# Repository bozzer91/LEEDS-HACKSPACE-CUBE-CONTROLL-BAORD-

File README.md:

# LEEDS HACKSPACE CUBE CONTROLL BOARD

# This READ me is a work in progress, please check back soon  :

This repository is for the new control board for the Leeds hackspace Cube art installation, this board will take input from a pc and output commands to the 16 Lines of addressable LEDS at 5v logic.  

wiring diagram visualisation ( not final revision) 

( the cube ) 

## Board info :

### Purpose : 
This control board is designed to take a Raspberry pi pico / pico-W and convert 16 data lines from 3v3 voltage to 5volt data and output this to the 16 LED strings of the Hackspace Cube. this board also includes extra ports for expansion and other functions for future upgrades. the board is about 10cm by 6cm and is deigned to be placed into an encloser with the users connectors of choice attached and soldered onto the PCB DATA outputs.   

### Reference text: 

The test points for the DATA and GPIO are as follows.
Data: to the left-hand side of the resistor above " D-1 example " the label. the left hand side is 5v

GPIO: test point to the right-hand side of the resistor below the labelling. with the left hand side being 3v3 volts

see below for the visual.

### Spare pin header :
The pin header by pins 16-28 are spare for future expansion of the cube the numbers listed on the PCB are the GPIO numbers of the pico. There are extra GND pins to the right of this pin header.

### Smothing caps :
There are 100nf smoothing caps on the main voltage rails for 5v and 3v3 these are set at locations around the board first set next to the pico and then one set pure bank of 4 logic shifters. ( see below images for examples )

### Main outputs : 
The controller board has two main Data output connectors in the form of two sets of pinheaders to connect to the users connector of choice this also mimicked the original breadboard design and allows for drop in replacement if required using the original ribbon cables. 

Connector 1 = Data 1-8 plus one GND pin
Connector 2 = Data 9-16 plus one GND pin

### Power : 
This controller board is powered by the Pico's usb input port. 

## History of this project: 

So some history of this project. back in 2022 ( give or take a covid lockdown ) it was found that the original micro controller board for the cube had broken. work was undertaken to revers engineer this board and make a replacement for 2022 Leeds lightweight. roll on to 2025 and we are still using the fear inducing Bread board that looks like something you find in a suite case in a mission impossible film that needs defusing ( see below image ) so when packing down the cube i decided to make a pcb to replace this and help move the Cube to a more user friendly plug and play design. 

BREAD BOARD

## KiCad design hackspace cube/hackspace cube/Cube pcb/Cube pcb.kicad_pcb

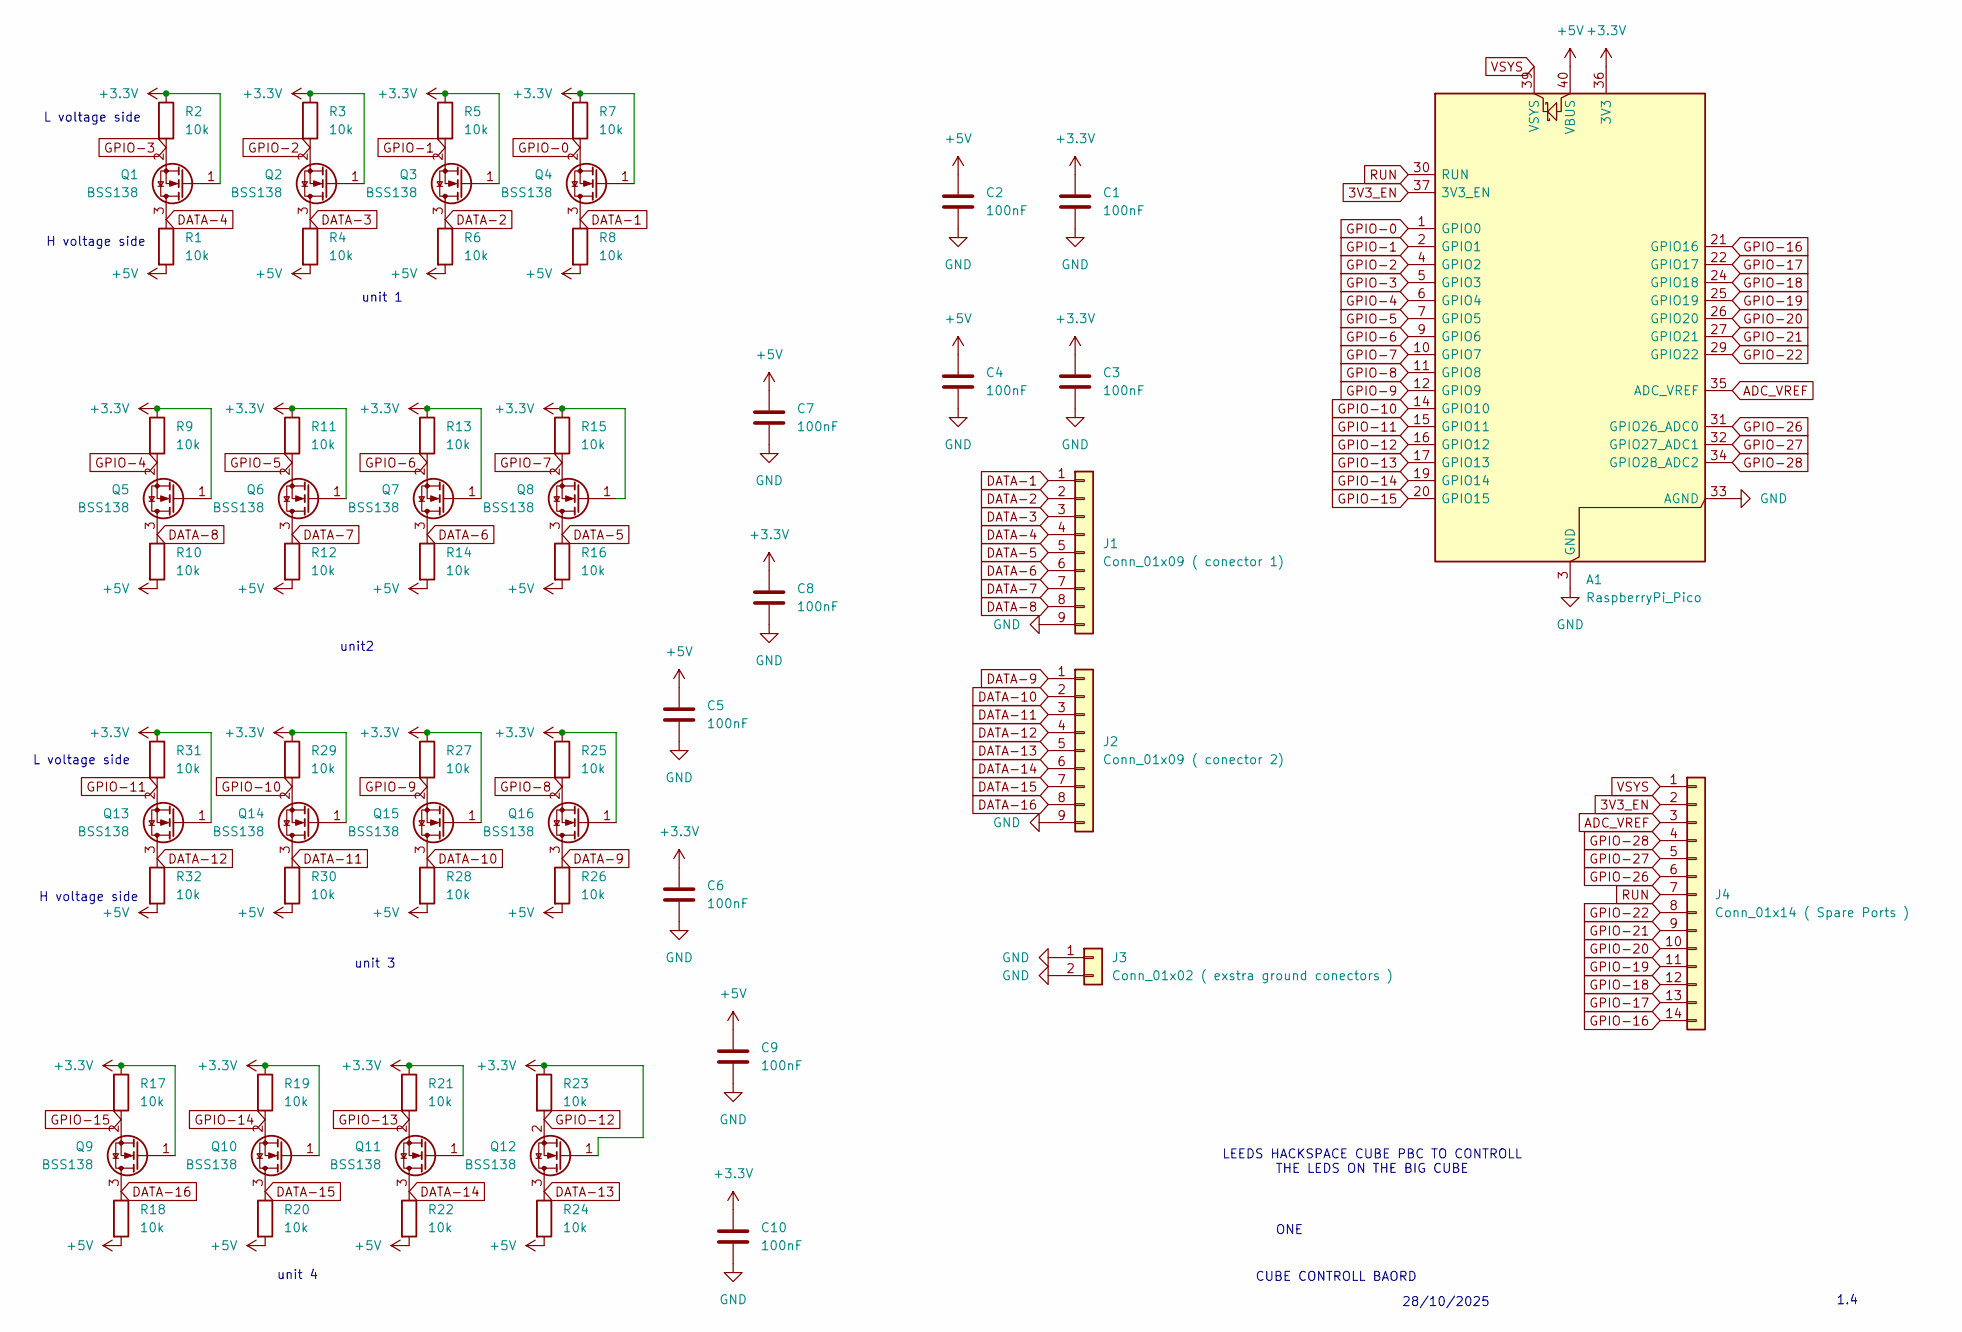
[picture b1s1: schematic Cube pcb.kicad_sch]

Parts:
A1: RaspberryPi_Pico; RaspberryPi_Pico_Common_Unspecified
C1, C2, C3, C4, C5, C6, C7, C8, C9, C10: 100nF; C_0805_2012Metric
J1: Conn_01x09 ( conector 1); PinHeader_1x09_P2.54mm_Vertical
J2: Conn_01x09 ( conector 2); PinHeader_1x09_P2.54mm_Vertical
J3: Conn_01x02 ( exstra ground conectors ); PinHeader_1x02_P2.54mm_Vertical
J4: Conn_01x14 ( Spare Ports ); PinHeader_1x14_P2.54mm_Vertical
Q1, Q2, Q3, Q4, Q5, Q6, Q7, Q8, Q9, Q10, Q11, Q12, Q13, Q14, Q15, Q16: BSS138; SOT-23
R1, R2, R3, R4, R5, R6, R7, R8, R9, R10, R11, R12, R13, R14, R15, R16, R17, R18, R19, R20, R21, R22, R23, R24, R25, R26, R27, R28, R29, R30, R31, R32: 10k; R_0805_2012Metric

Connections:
3V3_EN: A1.37 (3V3_EN), J4.2
+3.3V: A1.36 (3V3), C1.1, C3.1, C6.1, C8.1, C10.1, Q1.1 (G), Q2.1 (G), Q3.1 (G), Q4.1 (G), Q5.1 (G), Q6.1 (G), Q7.1 (G), Q8.1 (G), Q9.1 (G), Q10.1 (G), Q11.1 (G), Q12.1 (G), Q13.1 (G), Q14.1 (G), Q15.1 (G), Q16.1 (G), R2.1, R3.1, R5.1, R7.1, R9.1, R11.1, R13.1, R15.1, R17.1, R19.1, R21.1, R23.1, R25.1, R27.1, R29.1, R31.1
+5V: A1.40 (VBUS), C2.1, C4.1, C5.1, C7.1, C9.1, R1.2, R4.2, R6.2, R8.2, R10.2, R12.2, R14.2, R16.2, R18.2, R20.2, R22.2, R24.2, R26.2, R28.2, R30.2, R32.2
ADC_VREF: A1.35 (ADC_VREF), J4.3
DATA-1: J1.1, Q4.3 (D), R8.1
DATA-2: J1.2, Q3.3 (D), R6.1
DATA-3: J1.3, Q2.3 (D), R4.1
DATA-4: J1.4, Q1.3 (D), R1.1
DATA-5: J1.5, Q8.3 (D), R16.1
DATA-6: J1.6, Q7.3 (D), R14.1
DATA-7: J1.7, Q6.3 (D), R12.1
DATA-8: J1.8, Q5.3 (D), R10.1
DATA-9: J2.1, Q16.3 (D), R26.1
DATA-10: J2.2, Q15.3 (D), R28.1
DATA-11: J2.3, Q14.3 (D), R30.1
DATA-12: J2.4, Q13.3 (D), R32.1
DATA-13: J2.5, Q12.3 (D), R24.1
DATA-14: J2.6, Q11.3 (D), R22.1
DATA-15: J2.7, Q10.3 (D), R20.1
DATA-16: J2.8, Q9.3 (D), R18.1
GND: A1.3 (GND), A1.8 (GND), A1.13 (GND), A1.18 (GND), A1.23 (GND), A1.28 (GND), A1.33 (AGND), A1.38 (GND), C1.2, C2.2, C3.2, C4.2, C5.2, C6.2, C7.2, C8.2, C9.2, C10.2, J1.9, J2.9, J3.1, J3.2
GPIO-0: A1.1 (GPIO0), Q4.2 (S), R7.2
GPIO-1: A1.2 (GPIO1), Q3.2 (S), R5.2
GPIO-2: A1.4 (GPIO2), Q2.2 (S), R3.2
GPIO-3: A1.5 (GPIO3), Q1.2 (S), R2.2
GPIO-4: A1.6 (GPIO4), Q5.2 (S), R9.2
GPIO-5: A1.7 (GPIO5), Q6.2 (S), R11.2
GPIO-6: A1.9 (GPIO6), Q7.2 (S), R13.2
GPIO-7: A1.10 (GPIO7), Q8.2 (S), R15.2
GPIO-8: A1.11 (GPIO8), Q16.2 (S), R25.2
GPIO-9: A1.12 (GPIO9), Q15.2 (S), R27.2
GPIO-10: A1.14 (GPIO10), Q14.2 (S), R29.2
GPIO-11: A1.15 (GPIO11), Q13.2 (S), R31.2
GPIO-12: A1.16 (GPIO12), Q12.2 (S), R23.2
GPIO-13: A1.17 (GPIO13), Q11.2 (S), R21.2
GPIO-14: A1.19 (GPIO14), Q10.2 (S), R19.2
GPIO-15: A1.20 (GPIO15), Q9.2 (S), R17.2
GPIO-16: A1.21 (GPIO16), J4.14
GPIO-17: A1.22 (GPIO17), J4.13
GPIO-18: A1.24 (GPIO18), J4.12
GPIO-19: A1.25 (GPIO19), J4.11
GPIO-20: A1.26 (GPIO20), J4.10
GPIO-21: A1.27 (GPIO21), J4.9
GPIO-22: A1.29 (GPIO22), J4.8
GPIO-26: A1.31 (GPIO26_ADC0), J4.6
GPIO-27: A1.32 (GPIO27_ADC1), J4.5
GPIO-28: A1.34 (GPIO28_ADC2), J4.4
RUN: A1.30 (RUN), J4.7
VSYS: A1.39 (VSYS), J4.1

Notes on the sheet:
CUBE CONTROLL BAORD
unit 4
LEEDS HACKSPACE CUBE PBC TO CONTROLL THE LEDS ON THE BIG CUBE
unit 1
unit2
28/10/2025
unit 3
1.4
H voltage side
ONE
L voltage side

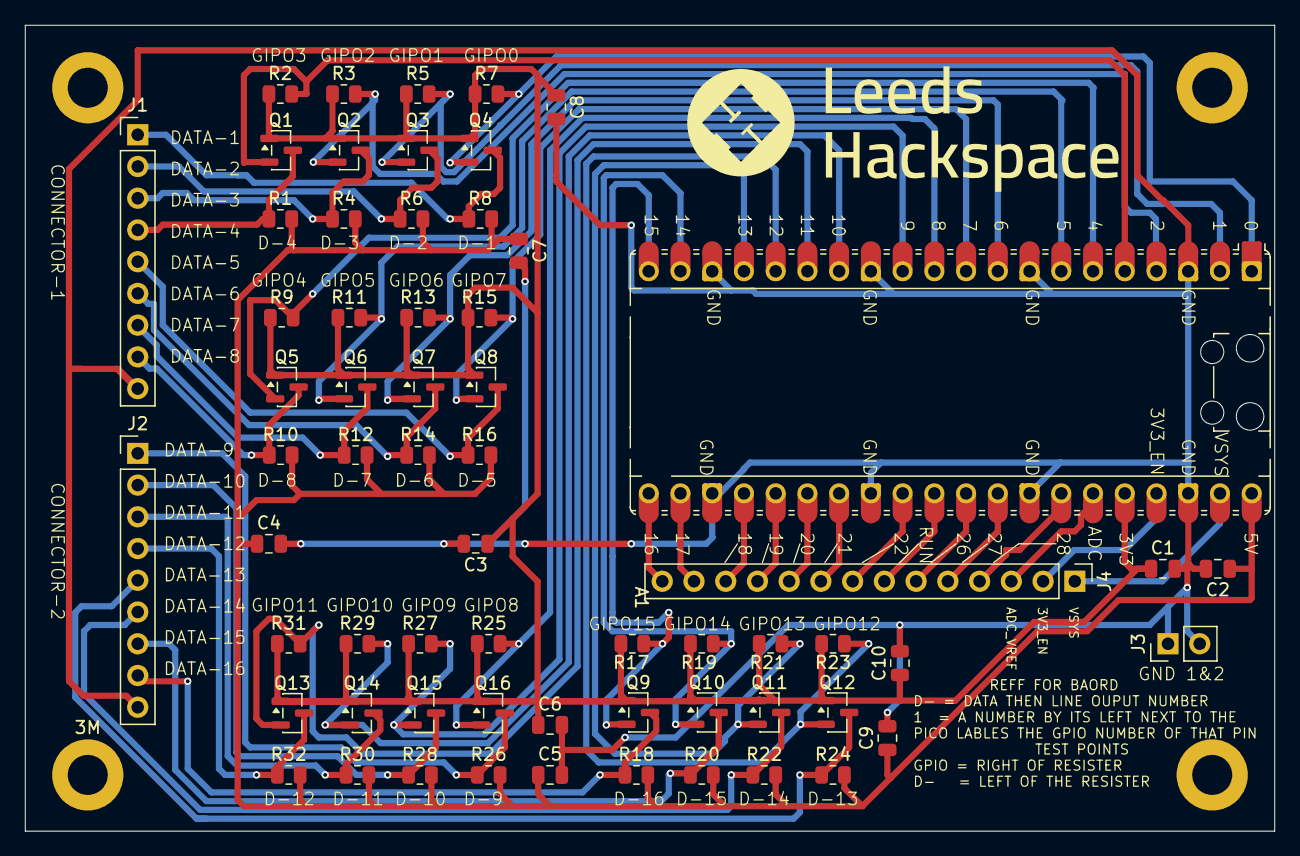
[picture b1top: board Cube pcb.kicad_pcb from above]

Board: 2 copper layers, 100.0 x 64.5 mm, 64 parts (0 on the bottom side), 49 nets.

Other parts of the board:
3M: MountingHole_3.2mm_M3_ISO7380_Pad

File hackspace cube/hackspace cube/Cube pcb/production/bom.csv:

Designator,Footprint,Quantity,Value,LCSC Part #
"_3, _2, ",,3,,
A1,RaspberryPi_Pico_Common_Unspecified,1,RaspberryPi_Pico,
"C1, C10, C2, C3, C4, C5, C6, C7, C8, C9",0805,10,100nF,
J1,PinHeader_1x09_P2.54mm_Vertical,1,Conn_01x09 ( conector 1),
J2,PinHeader_1x09_P2.54mm_Vertical,1,Conn_01x09 ( conector 2),
J3,PinHeader_1x02_P2.54mm_Vertical,1,Conn_01x02 ( exstra ground conectors ),
J4,PinHeader_1x14_P2.54mm_Vertical,1,Conn_01x14 ( Spare Ports ),
"Q1, Q10, Q11, Q12, Q13, Q14, Q15, Q16, Q2, Q3, Q4, Q5, Q6, Q7, Q8, Q9",SOT-23,16,BSS138,
"R1, R10, R11, R12, R13, R14, R15, R16, R17, R18, R19, R2, R20, R21, R22, R23, R24, R25, R26, R27, R28, R29, R3, R30, R31, R32, R4, R5, R6, R7, R8, R9",0805,32,10k,

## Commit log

2025-10-25 Update README.md
    EDIT READ ME
2025-10-25 CUBE KI CAD FILES
2025-10-25 rev 1.1
    added caps
2025-10-25 rev1.2 with pcb
    starting on pcb design
2025-10-26 updating pcb
    updating pcb most pins attached
2025-10-26 pcb first draft
2025-10-26 Update README.md
    UPDATING WITH INFO ON THE PCB
2025-10-26 Update README.md
    ADDING CURRECT IMAGE
2025-10-26 update pcb
    i have added labels and basic info onto the pcb
2025-10-26 Update README.md
    added image
2025-10-27 updated wiring D and PCB
    wiring D now has GND on the connector pins . PCB now has new shorter design to make it 10cm wide just need to add ground plain
2025-10-27 new pcb file
    new pcb file to add ground plain before sending off
2025-10-27 ground plain added
    ground plain added
2025-10-28 rev 1.4
    added new smooth caps and updated pcb
2025-10-28 DRC check done
2025-10-29 pcb fab files
    new test pcb fab files created
2025-10-29 Update README.md
    upadeting reedme
2025-10-31 updated spelling
    updated spelling using NavSpellCheck
2025-10-31 fixed more spelling
2025-11-18 Update README.md
    checking formatting
2025-11-19 Update README.md
    update test
2025-11-19 update text
2025-11-19 Update README.md
    update photos
2025-11-19 read me update
2025-11-19 updating readme
2025-11-19 Update README.md
    adding images
2025-11-19 edited read me and addeed image
    edited read me and addeed full size image files for easy reference

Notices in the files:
hackspace cube/hackspace cube/Cube pcb/Cube pcb.kicad_pcb:
LICENCE: OPEN SOURCE
